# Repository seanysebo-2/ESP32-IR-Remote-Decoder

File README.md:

# ESP32 IR Remote Controller | Custom PCB Design

## Project Overview

This project focuses on developing an ESP32-based infrared remote controller capable of receiving, decoding, storing, and transmitting infrared signals.

I initially developed and tested the circuit using a breadboard before transitioning to a custom PCB design using KiCad.

The goal of this project is to gain hands-on experience with electronics, microcontrollers, PCB layout, and hardware development.

## Components and Software

- ESP32 Development Board
- Infrared Receiver and Transmitter
- Tactile Push Buttons
- Resistors and Breadboard
- KiCad PCB Design Software
- Arduino IDE
- Arduino IRremote Library

## Project Development

### Phase 1: Breadboard Prototyping

Developed a working ESP32-based circuit capable of receiving and decoding infrared signals using the Arduino IRremote library.

Implemented functionality for storing received infrared commands and transmitting them through an infrared LED.

### Phase 2: Custom PCB Design

Designed a custom PCB using KiCad to transition the project from a breadboard prototype to a more permanent hardware platform.

The PCB design includes:

- ESP32 development board connections
- Infrared receiver and transmitter connections
- Four tactile push buttons
- Copper trace routing and ground planes
- Component footprints and placement
- Design Rule Check (DRC) verification

### Phase 3: Manufacturing and Assembly

The PCB design has been prepared for manufacturing. The next stage involves assembling the physical components and testing the completed board.

## Skills Demonstrated

- Printed Circuit Board (PCB) Design
- KiCad
- Circuit Prototyping
- Electronic Troubleshooting
- ESP32 Microcontroller Development
- Hardware Design and Verification

## Future Improvements

- Assemble and test the manufactured PCB
- Verify button functionality and infrared transmission
- Improve the PCB layout based on physical testing
- Explore a more compact handheld enclosure

### Circuit Schematic

The schematic shows the ESP32 GPIO connections, infrared receiver and transmitter connections, and four tactile push buttons.

### PCB Layout and Routing

The PCB was designed in KiCad using front and back copper layers, component placement, copper trace routing, and ground planes.

### PCB 3D Visualization

The 3D model shows the physical PCB design and component placement.

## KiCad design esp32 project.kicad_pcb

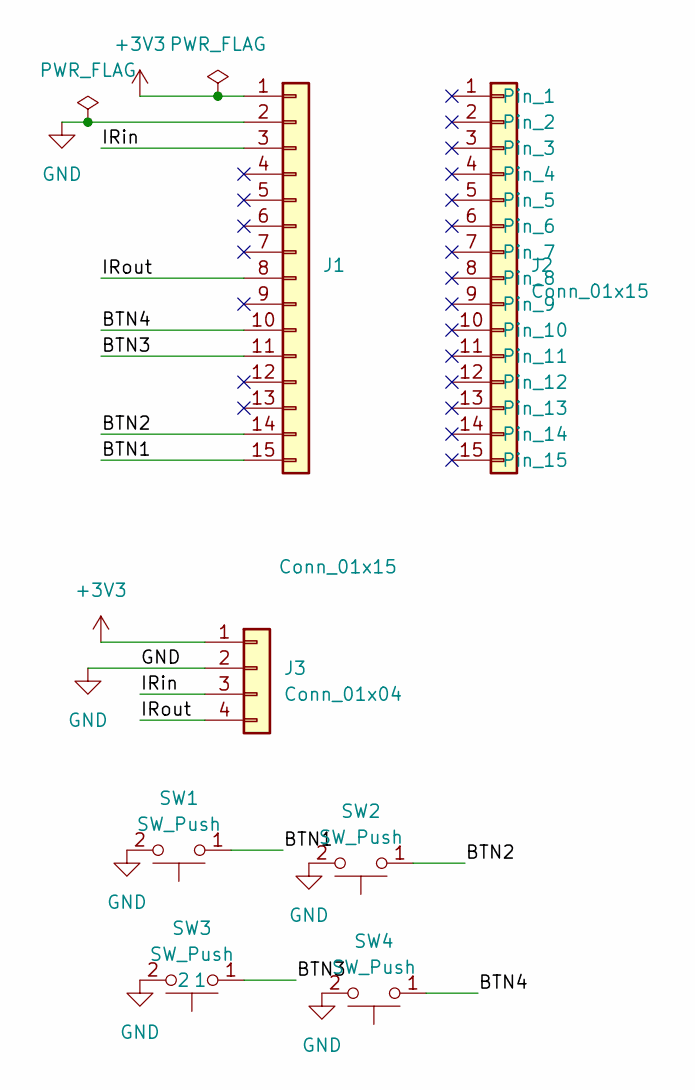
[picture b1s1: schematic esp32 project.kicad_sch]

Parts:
J1, J2: Conn_01x15; PinSocket_1x15_P2.54mm_Vertical
J3: Conn_01x04; PinHeader_1x04_P2.54mm_Vertical
SW1, SW2, SW3, SW4: SW_Push; SW_Tactile_SMD_10x10mm

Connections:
+3V3: J1.1, J3.1
/BTN1: J1.15, SW1.1
/BTN2: J1.14, SW2.1
/BTN3: J1.11, SW3.1
/BTN4: J1.10, SW4.1
/IRin: J1.3, J3.3
/IRout: J1.8, J3.4
GND: J1.2, J3.2, SW1.2, SW2.2, SW3.2, SW4.2

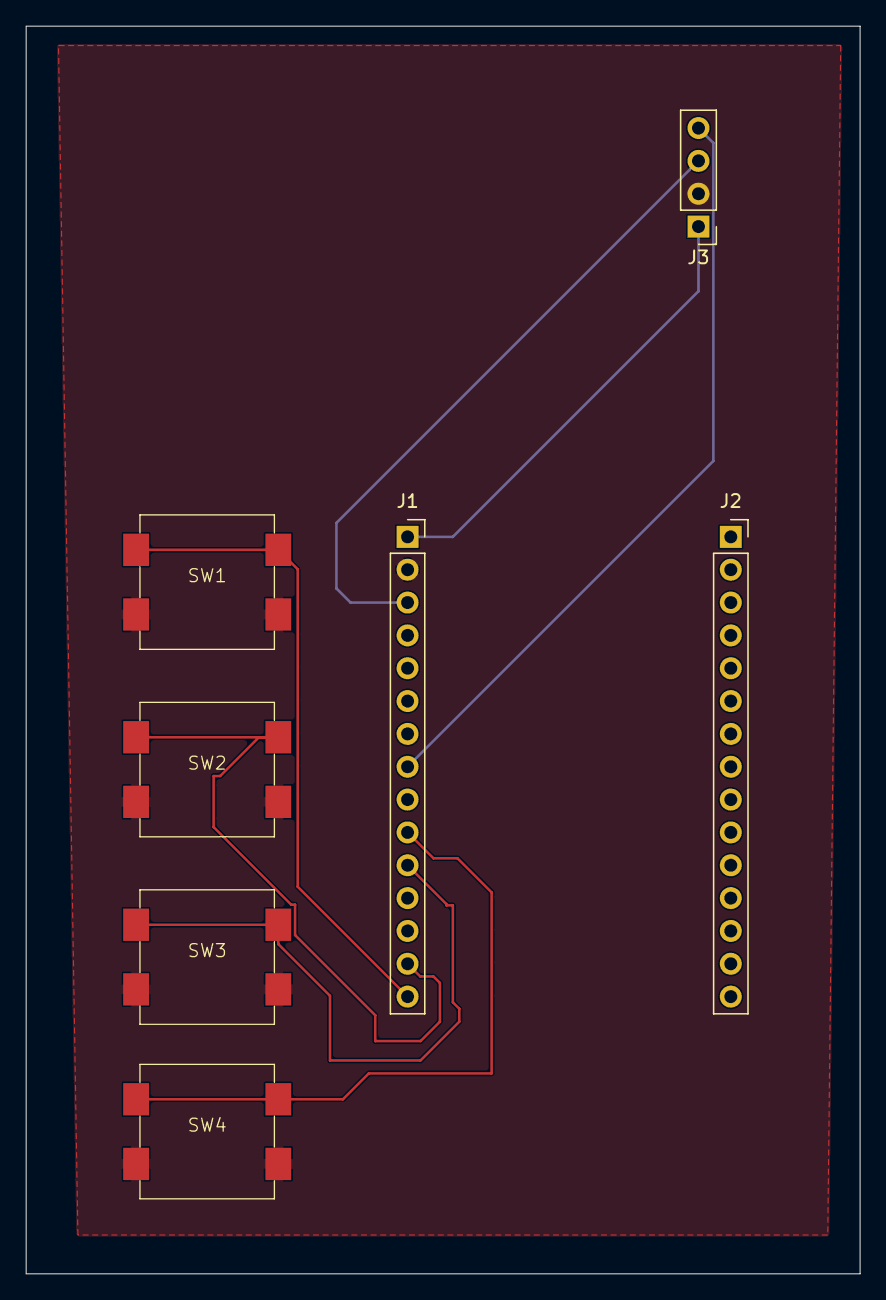
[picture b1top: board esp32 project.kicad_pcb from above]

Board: 2 copper layers, 64.5 x 96.5 mm, 7 parts (0 on the bottom side), 8 nets.
